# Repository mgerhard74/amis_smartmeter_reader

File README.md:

# AMIS Lesegerät für die NetzOÖ Smartmeter Kundenschnittstelle

Der AMIS Leser ist ein kostengünstiger, autonomer, Cloud-free Lesekopf auf ESP8266 Basis, um den NetzOÖ Smartmeter Siemens TD-3511/TD-3512 per Wifi auszulesen. (Zählwerke, aktueller Verbrauch/Einspeisung)
Dies ist für Hausautomatisierungen oder PV geregelte Verbrauchssteuerungen (Eigenverbrauchsoptimierung; E-Auto laden; Nulleinspeisung) sehr hilfreich, oder auch nur, um den aktuellen Leistungsbezug in Echtzeit abzufragen.

Es steht ein Webinterface mit allen wichtigen Werten und zur Parametereinstellung zur Verfügung, per REST API können die aktuellen Zähler- und Verbrauchsdaten im JSON-Format abgerufen werden, per MQTT an einen Broker weitergegeben, per Modbus/TCP abgerufen werden oder an ThingSpeak hochgeladen werden. Die grafische Ansicht der historischen ThingSpeak Daten ist über einen Menüpunkt im Webinterface möglich.
Der NetzOÖ Smartmeter gibt Daten im Sekundentakt aus, somit stehen jede Sekunde neue Daten (Zählerstände Verbrauch und Einspeisung, aktueller Bezug/Einspeisung, Saldo aus Bezug-Einspeisung) zur Verfügung.

Der Amis Leser benötigt eine 5V Spannungsversorgung (max. 0,13A, typ. 0,075A; Leistungsaufnahme < 1W) durch ein Micro-USB Netzteil und wird magnetisch durch 3 Magnete, die an der Platinenunterseite angeklebt sind, an der optischen Kundenschnittstelle des Siemens Smartmeter gehalten.

Der AMIS Leser emuliert auch einen Fronius Smartmeter (nur Einspeisepunkt Adresse 1) per Modbus/TCP für einen Fronius Symo (ab Datamanager Version 3.28.1-3) oder Gen24 Wechselrichter. Siehe dazu Docs/AmisFroniusSmartmeter.pdf.
Ebenso kann ein Shelly Smartmeter (Pro 3EM, Pro EM-50, EM Gen3) emuliert werden, wie ihn viele Balkonkraftwerksspeicher für die Nulleinspeisung erwarten. Dafür stehen zwei Varianten zur Verfügung, die auch gemeinsam aktiv sein können:
- "RPC over UDP" für Speicher vom Typ B2500 (z.B. Marstek Saturn), die den Shelly per UDP-Broadcast abfragen.
- "RPC over HTTP" für Speicher, die den Shelly per mDNS im Netzwerk suchen und danach per HTTP abfragen (z.B. Solakon One, Hoymiles, Anker). Der Leser meldet sich dabei als `_http._tcp`/`_shelly._tcp` an und beantwortet unter seiner normalen Webserver-Adresse zusätzlich `/shelly` sowie `/rpc/<Methode>` (`EM.GetStatus`, `EMData.GetStatus`, `EM.GetConfig`, `Shelly.GetDeviceInfo`, `Shelly.ListMethods`, bzw. die `EM1.*` Varianten bei einphasigen Geräten).
  Findet ein Speicher den Leser nicht, kann optional der Shelly-Name (z.B. `ShellyPro3EM-8C4F0044B70B.local`) als mDNS-Hostname verwendet werden - für Geräte, die diesen Namen direkt auflösen statt dem SRV-Eintrag zu folgen. `<Gerätename>.local` ist dann nicht mehr auflösbar, da der ESP8266 nur einen mDNS-Hostnamen führen kann.

In der aktuellen Version ist es auch möglich eine (Tasmota-, Shelly-)Wifi Steckdose aufgrund von PV Überschuss anzusteuern. ("Ein" unter Saldowert; "Aus" über Saldowert; Url für Ein bzw Aus)
Ein aus dem Bezugszählerstand errechneter 1/4h Spitzenverbrauchswert des aktuellen und Vormonats ist nun auch hinzugefügt worden, dieser ist ab 2027 für den lastabhängigen Teil der Netzgebühr interessant.

Startseite Webinterface:

## Highlights
- Webinterface (Einstellungen, Updates)
- Schnittstellen: RestApi, MQTT, ModbusTCP, Upload zu Thingspeak
- Wifi Sleep Mode, Neustart bei Ping-Fehler, Schaltet eine Tasmota Steckdose bei PV Überschuss, Emuliert einen Fronuis Smartmeter per ModbusTCP, Emuliert einen Shelly Smartmeter per UDP und HTTP

## Inbetriebnahme
Der Amis-ESP8266 läuft normalerweise im Station-Mode, d.h. der ESP8266 verbindet sich als Client mit einem Wlan Router/AP. Dazu muss er aber erst einmal die SSID und das Wlan Passwort kennen. Daher wird der ESP8266 zur Einrichtung in den AP-Mode (Access-Point) versetzt. Das geschieht, indem man mit gesetztem Jumper (Steckbrücke) bootet.
Mit einem Handy, Tablett oder Notebook kann man das WiFi-Netz "ESP8266_AMIS" verbinden. Nach dem Verbinden einen Web-Browser starten und als Adresse http://192.168.4.1 eingeben. Menü / Wifi wählen und Netzwerkeinstellungen vornehmen, wir empfehlen dem AMIS Leser eine fixe IP zu geben, damit ist er immer mit der gleichen IP in deinem Netzwerk erreichbar. Gateway- und Namenserver-IP Adresse sind u.a. für Thingspeak notwendig.
Ev. auch gleich den AMIS/MBUS-Schlüssel vom NetzOÖ Portal (siehe dazu docs\AmisMBUSKey.pdf) eingeben, auf Allgemein "ThingSpeak/Highcharts aktiv" vorläufig nicht aktivieren. Jumper/Steckbrücke nun öffnen/abziehen und rebooten, nun sollte der Amis Leser über die gewählte IP erreichbar sein. Erzeugt er wieder das Wlan Netz "ESP8266_AMIS", obige Schritte wiederholen, vielleicht wurden Daten falsch eingegeben.
Der Amis Leser muss mit dem USB Port nach oben bzw schräg rechts unten (je nach Hardwareversion) an den richtigen (AMIS/MBUS Key) Siemens TD3511 magnetisch angeheftet werden.
RFPower ermöglicht die Kontrolle über die Sendeleistung, wobei weniger Sendeleistung anzuraten ist. 0dBm ist 1mW, was für kleinere Entfernungen genügt. Maximal 20dBm.
Sind die Einstellungen (vor allem der MBUS Key aus dem NetzOÖ Portal) korrekt, dann sollten unter Zähler Werte angezeigt werden. Wenn die Entschlüsselung der Daten unplausible Daten erzeugt, wird dies durch eine Meldung "falscher MBUS Key" angezeigt. Es dauert 1-2 Minuten bis Zähler und ESP synchron sind. Die Leds für TxD (nur Hardware V1) und RxD blinken dann im Sekundentakt.

## AMIS Hardware. PCB von Jlcpcb, händisch bestückt und gelötet:

## AMIS Hardware V2. Maschinell bestückt und gelötet von Jlcpcb:

## 31mm Drahtantenne verbessert Wifi Konnektivität um ca 8dB:
Man kann ganz einfach die Wifi Konnektivität verbessern, in dem man die PCB Antenne auftrennt und einen Draht wie am Bild anlötet.

## Danksagung
Vielen Dank an Gottfried Prandstetter für die grandiose Entwicklungsarbeit an diesem Projekt. Er stellt die Soft- und Hardware als open-source zur Verfügung.
Vielen Dank auch die TechnikerInnen hier auf Github für eure Unterstützung.

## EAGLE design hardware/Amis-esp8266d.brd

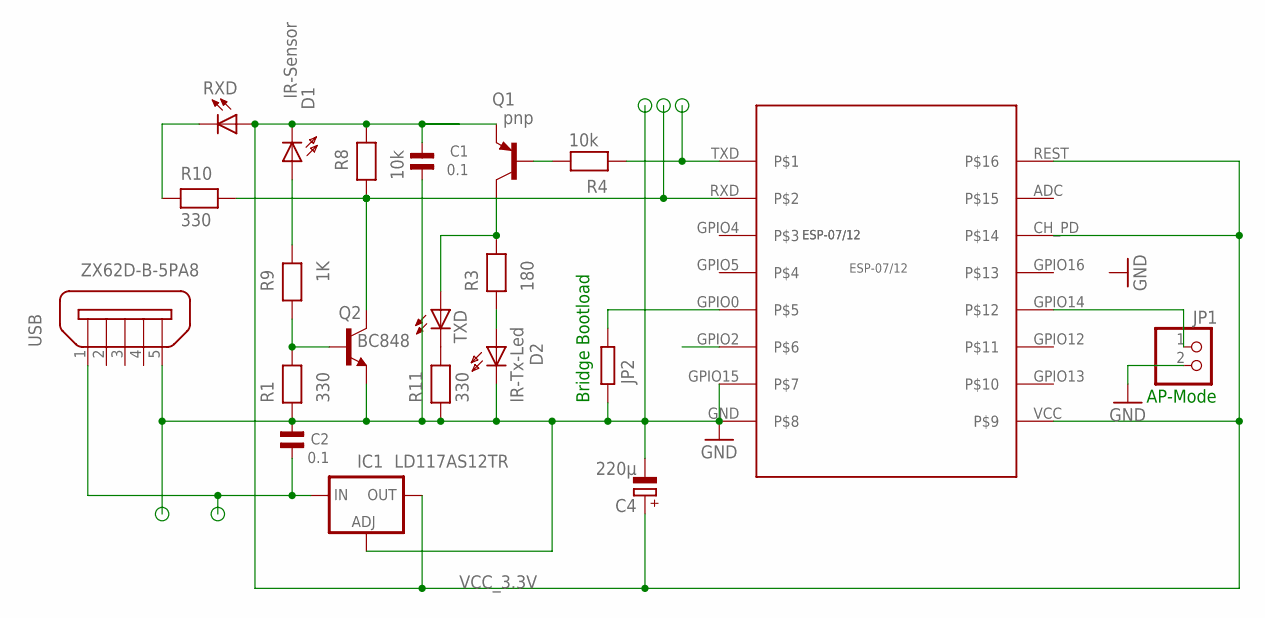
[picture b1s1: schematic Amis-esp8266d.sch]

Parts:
C1, C2: 0.1; 0805W
C4: 220µ; 153CLV-0605
D1: IR-Sensor; HSMXC670
D2: IR-Tx-Led; HSMXC670
IC1: LD117AS12TR; SOT223
JP1: PINHD-1X2; 1X02
JP2: R-EU_R1210W; R1210W
Q1: pnp; SOT23
Q2: BC848; SOT23
R1, R10, R11: 330; 0805W
R3: 180; 0805W
R4, R8: 10k; 0805W
R9: 1K; 0805W
RXD: LEDSML0805; SML0805
TXD: LEDSML0805; SML0805
U$2: ESP-07/12
USB: ZX62D-B-5PA8

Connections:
DC1: C2.1, IC1.3 (IN), USB.1
GND: C1.1, C2.2, C4.-, D2.K (C), IC1.1 (ADJ), JP1.2, JP2.1, Q2.2 (E), R1.1, R11.1, U$2.GND, U$2.GPIO15, USB.5
unnamed: Q1.3 (C), R3.2, TXD.A
unnamed: Q1.1 (B), R4.2
unnamed: D2.A, R3.1
unnamed: D1.A, R9.2
unnamed: Q2.3 (C), R8.1, R10.2, U$2.RXD
unnamed: Q2.1 (B), R1.2, R9.1
unnamed: JP1.1, U$2.GPIO14
unnamed: R4.1, U$2.TXD
unnamed: JP2.2, U$2.GPIO0
unnamed: R10.1, RXD.C
unnamed: R11.2, TXD.C
TXD1: U$2.GPIO2
VCC_3.3V: C1.2, C4.+, D1.K (C), IC1.4 (OUT), Q1.2 (E), R8.2, RXD.A, U$2.CH_PD, U$2.REST, U$2.VCC

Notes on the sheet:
Bridge Bootload
AP-Mode

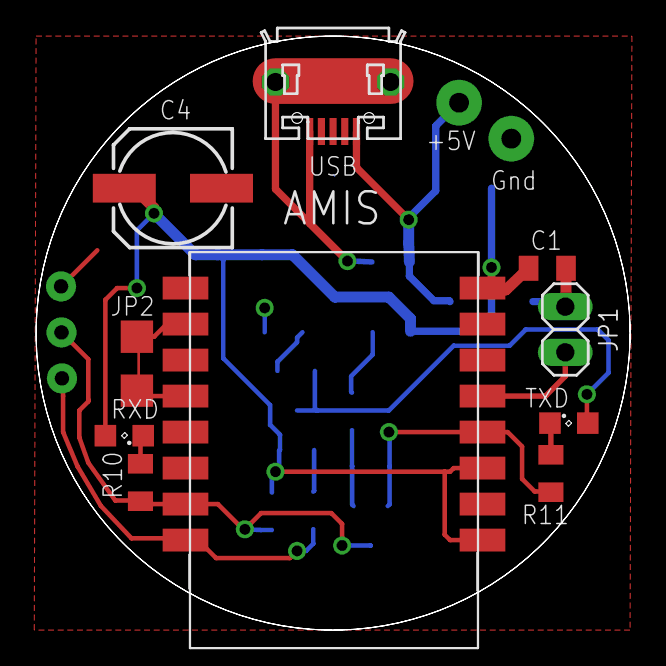
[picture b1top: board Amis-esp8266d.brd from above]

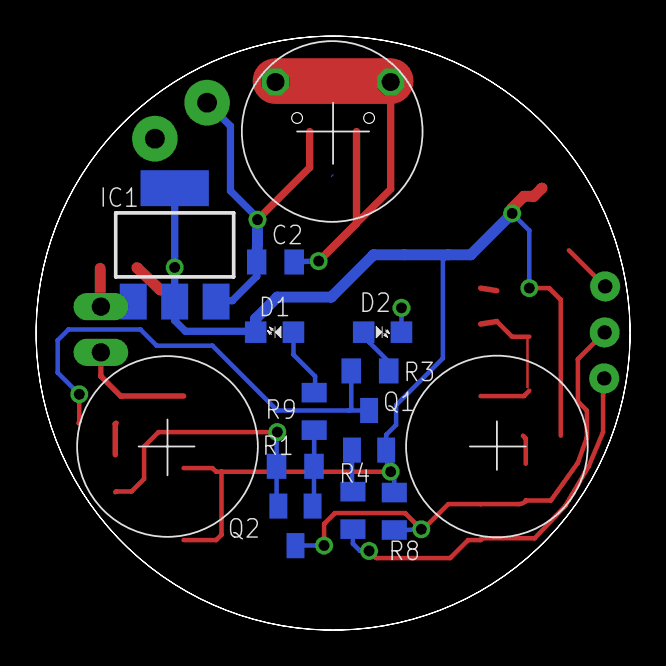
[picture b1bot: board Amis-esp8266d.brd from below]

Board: 2 copper layers, 33.0 x 33.0 mm, 21 parts (11 on the bottom side), 14 nets.

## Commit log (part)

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2026-02-09 initial commit (first tests successful)
2026-02-09 corrected decription (now ESP-ID)
2026-02-09 fixed unsecure char*, removed unused vars, fixed programming style(namings, early exit)
2026-02-09 removed 'writeEvent' entries (were for debugging)
2026-02-09 optimized/changed device selection, var namings, init, fixed jsonBuffer
2026-02-09 fixed dynamic buffer init ( possible stack overflow), switched to StaticJsonBuffer
2026-02-09 added timing to debug string
2026-02-09 changed AP_PIN check/Network init to make pin usable for SoftwareSerial, changed DBG macro to add newline and updated DBG calls
2026-02-09 updated defaults
2026-02-09 added Debug output to Logging
2026-02-09 removed invalid va_end()
2026-02-10 Fix: NetworkClass::getValidHostname() - Don't become an endless loop.
    This should address issue 42 (
    https://github.com/mgerhard74/amis_smartmeter_reader/issues/41 )
2026-02-10 Webclient: Diplay Log - If no time available display runtime instead
2026-02-10 NFC: Rename macro AMIS_DEVELOPER_MODE to AMIS_BUILTIN_CONFIGURATION
2026-02-10 Webclient: Display BSSIDs in Wifi-Scan-Result.
2026-02-10 WifiScan: Release buffer early.
2026-02-10 patch_apply.py: Patches MUST apply successful.
2026-02-10 Log: Rename function and macros
2026-02-10 mqtt: Log publish() infos in verbose mode.
2026-02-10 Log: Prepare - configure loglevel per module.
2026-02-10 Network: Change loglevel of 'Wifi sleep mode disabled' message
2026-02-10 Webclient: Display connected BSSID in status page.
2026-02-10 Websocket: Remove command 'print2' which does nothing.
2026-02-10 RemoteOnOff: Fix - Use returned reference instead pointer.
2026-02-10 ThingSpeak: Don't try sending if WiFi is disconnected
2026-02-10 Exception: Replace core_esp8266_postmortem.cpp within framwork with own module.
    The device is mostly located in the fuse box without any connected
    computer.
    The serial of the device is used to communicate with the electric meter
    and dealing with baudrates of 300 or 9600 which disturbs the serial
    exception dump.
    Also working with low baudrates can trigger the hardware watchdog while
2026-02-10 Cleanup: Remove STROMPREIS define and related code.
2026-02-10 Webclient: Use correct initalizing type.
2026-02-10 Exception: Play a bit generating some exceptions
2026-02-10 NFC: Prefer isEmpty() vs comparing with ""
2026-02-10 Remove unneeded data from logfile.
2026-02-10 AmisReader: Try syncing with counter faster
2026-02-10 EEPROM Clear: set to 0xff which is default for a formatted eeprom
2026-02-10 Exception: Dump always 4 addresses into one line.
2026-02-10 NFC: Adapt varname in AMIS_DEVELOPER_MODE
2026-02-10 Log: Allow adjusting loglevel via websocket.
2026-02-10 Import core_esp8266_postmortem.cpp
    Preperation of framework replacement
    Import from
    https://raw.githubusercontent.com/esp8266/Arduino/refs/tags/3.1.2/cores/esp8266/core_esp8266_postmortem.cpp
    See:
    https://github.com/esp8266/Arduino/blob/3.1.2/cores/esp8266/core_esp8266_postmortem.cpp
2026-02-10 Modbus: Add some verbose logging.
2026-02-10 Webclient: Remove unneeded line from 'week' table.
2026-02-10 Log: Use macros for logging ip addresses
2026-02-10 RemoteOnOff: Use timeout of 3.5 sec for tcp request.
2026-02-10 NFC: Remove declaration of deleted var from header file.
2026-02-10 NFC: ShellySmartmeterEmulation remove trailing spaces.
2026-02-10 Network: Reorder calls in onStationModeGotIP() and onStationModeDisconnected()
2026-02-10 Websocket command 'clear' removes also all logfiles.
2026-02-10 Adjust RebootAtMidnight every time we get a new timestamp.
2026-02-10 AmisReader: Fix: Faster sync with counter
2026-02-10 Exception dump: Don't become recursive
2026-02-10 Remove debugging stuff
    Use LOG_D, LOGF_D, LOG_V or LOGF_V macros instead.
    If format string should be in progmem, LOG_DP, LOGF_DP, LOG_VP or
    LOGF_VP macros should be used.
2026-02-10 Webserver/Rest: Return more readable and ccommon http header field.
2026-02-10 Revert "Exception: Limit stack dump depth to avoid timeout during exceptions."
    This reverts commit ee81df69a6e5679e5e8871ca1ab25ed42662ab7b.
2026-02-10 AmisReader: Call _serial->flush() even writing a single byte.
2026-02-10 NFC: Use std::size() checking array length.
2026-02-10 Config: Even load amis_key in AP-Mode but don't use any json parser.
    "Brutal" reading "amis_key" from /config.general even in AP-Mode.
    Tries to get an "amis_key" but tries to use as less as possible external
    libraries. This should avoid bricking the device with any wrong or
    invalid configuration.
2026-02-10 Logfile: Fix reading number of entries
2026-02-10 ThingSpeak: Adapt logging
2026-02-10 NFC: Silence cpplint warning
2026-02-10 Exception dump: Save addresses only once
2026-02-10 NFC: Source cleanup.
2026-02-10 Nicer serving website: /upgrade
2026-02-10 AmisReader: NFC - Use define, and add comments
2026-02-10 Networkconnection: Allow specifying WLAN channel.
2026-02-10 Log: Introduce _getModuleName().
2026-02-10 ThingSpeak: More accurate status strings
2026-02-10 Log: Prevent reading long log entries which could cause out-of-memory
2026-02-10 Don't use while() for shrinking string. Also use strlcat().
2026-02-10 Undo: NFC: Prepare patch_apply.py script to patch the whole framework.
2026-02-10 mqtt: Do not change replace object IPaddress - just change values
2026-02-10 Exception: Fallback writing - use information from ESP.getResetInfoPtr().
2026-02-10 RebootAtMidnight: Adapt logging
2026-02-10 MQTT: Only try connect if we have WiFi
2026-02-10 Exception: Limit stack dump depth to avoid timeout during exceptions.
    A workaround patch for the ESP8266 core.
    The standard ESP8266 exception dump via the serial interface is
    time-consuming, often preventing us from capturing exceptions in our
    system—especially since a serial interface is not always connected.
    This commit introduces a configuration value to the ESP8266 core,
    allowing us to limit the number of stack values processed and sent via
2026-02-10 WatchdogPing: Adapt logging
2026-02-10 Startup: Use ESP.getResetInfo() in log info
2026-02-10 Json: Release DynamicJsonBuffer early.
2026-02-10 Log: Adapt logging for itself
2026-02-10 Introduce LOG_x() and LOGxP() macros which works like print().
2026-02-10 NFC: Constify a variable.
2026-02-10 Use json.containsKey()
2026-02-10 Websocket: Log invalid requests
2026-02-10 Logfile: NFC - Update comments
2026-02-10 Shelly: Don't start listener in AP mode.
2026-02-10 Shelly: Adap logging.
2026-02-10 Shelly: Apply config change immediately.
2026-02-10 Shelly: Log error if starting listener fails.
2026-02-10 Bump version to v1.5.8
2026-02-14 NFC: Format code
2026-02-14 Fix: MQTT publish - export valid time
    As we have no ARDUINOJSON_USE_LONG_LONG json.print() converts a 64 bit
    value ist converted into boolean true,
2026-02-14 Update maintainer and contributing guides
2026-02-14 NFC: Source cleanup
2026-02-14 Statuspage: Don't convert value into string
2026-02-15 Rest vars being global <const char*>
2026-02-15 Stop ShellyEmulator in Reboot/Update sequence.
2026-02-15 removed DynamicJsonBuffer size declaration
2026-02-15 make cpplint with TODO(anyone) happy
2026-02-15 Serial output only on check() aka init
2026-02-21 MQTT: Don't bind onMessage() as it is only used to log a warning.
2026-02-21 Remove unneeded include <AsyncJson.h>.
2026-02-21 Allocate memory early when sending weekdata.
2026-02-21 ThingSpeak: Stop logging connection errors after 3 attemps
2026-02-21 Websocket: Queue client requests and process them via Ticker sendDataTaskCb()
    As onWebsocketEvent() is called from SDK in sys context (limited stack),
    client requests now get queued and processed them via Ticker function
    sendDataTaskCb().
2026-02-21 Workflow: Don't use special chars in README.txt
2026-02-21 Introduce RingBuffer class.
2026-02-21 Webserver/Dev-Function: Remove command dev-get-systemmonitor-stat
2026-02-21 MQTT: Stop logging connection errors after 3 attemps.
2026-02-21 Web-Statuspage: Split gereration data and display mem/stack stats.
    Preventing large memory amounts needed, split generation of data for the
    web-statuspage into chunks.
    Display memory & stack stats on the statuspage (only in developer mode)
2026-02-21 NFC: Set bool parameter explicit to true/false.
2026-02-21 Playground IROM, IRAM, TEXT
2026-02-21 NFC: Remove unused include.
2026-02-21 Loggpage requests: Use RingBuffer instead of std::list.
2026-02-21 Try making MQTT more stable
2026-02-21 WatchdogPing: Collect memory and stack stats
2026-02-21 Statuspage: Display status of DHCP and AP-Mode.
2026-02-21 Function clearHist() - Don't use String()
2026-02-21 Network: Use RingBuffer instead of std::list.
2026-02-21 Update async mqtt lib to latest develop version
    Changes:
    see
    https://github.com/marvinroger/async-mqtt-client/compare/v0.9.0...develop
2026-02-21 Statuspage: Display Firmware CRC32 cheksum
2026-02-21 Utils: Change collecting stack/context information
2026-02-21 Remove SYSTEMMONITOR_STAT()from main loop().
2026-02-21 Log: Display context in developer mode
2026-02-21 Websocket Async Handling: Allow processing requests from disconnected clients.
    Needed if client sends reboot request.
2026-02-21 Shelly-Emulator: Limit appendix to 16 chars
    As the whole device-id is limited to 26 and "shellyemg3" needs already
    10, we can limit the input to 16.
    Also String() is replaced with char[27] as 26 is max length of whole
    device id.
2026-02-21 Network: Start reconnecting in user context.
2026-02-21 WiFi: Stop logging connection errors after 3 attemps.
2026-02-21 Use only pop() in Ringbuffer and limit time in WebserverWsDataClass::sendDataTaskCb().
2026-02-22 Bump version to v1.5.9
2026-02-27 Bump actions/download-artifact from 7 to 8
    Bumps [actions/download-artifact](https://github.com/actions/download-artifact) from 7 to 8.
    - [Release notes](https://github.com/actions/download-artifact/releases)
    - [Commits](https://github.com/actions/download-artifact/compare/v7...v8)
    ---
    updated-dependencies:
    - dependency-name: actions/download-artifact
2026-03-04 NFC: Remove trailing spaces
2026-03-04 NFC: Add compiler attribute to force alignment of structure.
2026-03-04 Fialsafe: Force firmware filename to start with 'firmware' and ending with '.bin'
2026-03-04 NFC: Remove defines (development leftover)
2026-03-06 Failsafe mode: LED blinks in 2 sec interval
    This makes the active failsafe mode easier to recognize.
2026-03-16 NFC: Pass correct value to (currently unused) parameter
2026-03-16 NFC: Add comment
2026-03-16 Websocket command: softreset
    This forces an immediate reboot, regardless of any active firmware
    updates or ongoing rebooting states.
2026-03-16 Firmwareupdate: Stop MQTT really (Disable reconnecting)
2026-03-16 Fix: MQTT data stops getting published (issue #57).
    Fixes
    https://github.com/mgerhard74/amis_smartmeter_reader/issues/57
    Seems Ticker() class does not like a lot changes on an armed Ticker().
    Fast & ugly fix.
2026-03-24 Bump version to 1.6.0
2026-03-30 Log time sync only if diff is more than 1 sec.
2026-03-30 Log WiFi connection errors just 2 times.
2026-03-30 Log ThingSpeak connection errors just 2 times.
2026-04-05 Siemens Benutzerhandbuch TD-351x
2026-04-13 Bump softprops/action-gh-release from 2 to 3
    Bumps [softprops/action-gh-release](https://github.com/softprops/action-gh-release) from 2 to 3.
    - [Release notes](https://github.com/softprops/action-gh-release/releases)
    - [Changelog](https://github.com/softprops/action-gh-release/blob/master/CHANGELOG.md)
    - [Commits](https://github.com/softprops/action-gh-release/compare/v2...v3)
    ---
    updated-dependencies:
2026-05-01 Update ThingSpeak.cpp
    Fix für Thingspeak und Internetausfall (https://github.com/mgerhard74/amis_smartmeter_reader/issues/64 )
